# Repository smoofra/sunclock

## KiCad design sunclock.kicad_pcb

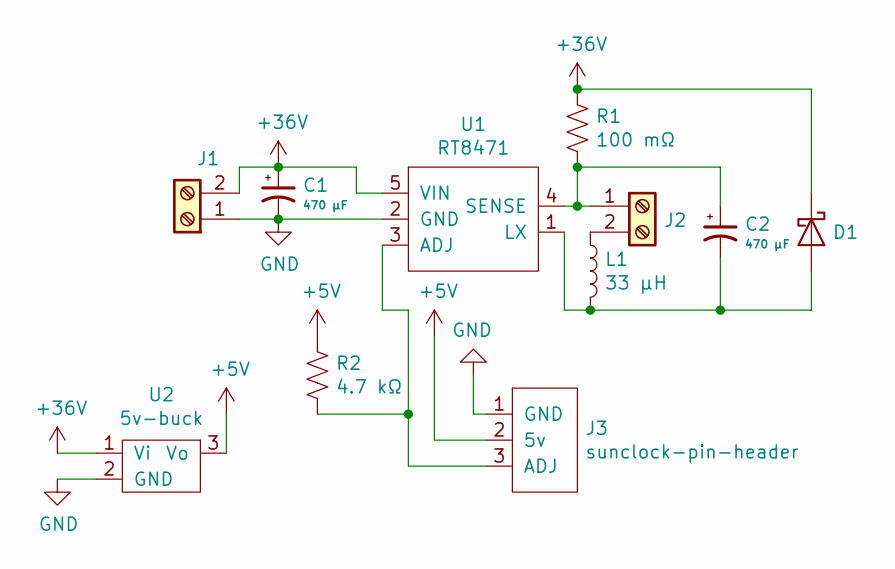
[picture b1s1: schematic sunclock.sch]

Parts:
C1, C2: 470 μF; CP_Radial_D8.0mm_P3.50mm; MPN RNE1C471MDN1PX
D1: D_Schottky; D_DO-41_SOD81_P10.16mm_Horizontal; MPN 11DQ04TR
J1, J2: Screw_Terminal_01x02; TerminalBlock_Phoenix_MKDS-1,5-2-5.08_1x02_P5.08mm_Horizont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; MPN 1935161
J3: sunclock-pin-header; SIP-3
L1: 33 μH; L_Radial_D8.7mm_P5.00mm_Fastron_07HCP; MPN RLB0914-330KL
R1: 100 mΩ; R_0402_1005Metric; MPN SR731ETTPR100F
R2: 4.7 kΩ; R_Axial_DIN0207_L6.3mm_D2.5mm_P10.16mm_Horizontal
U1: RT8471; TSOT-23-5_HandSoldering; MPN RT8471GJ5
U2: 5v-buck; SIP-3; MPN BP5277-50

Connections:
+5V: J3.2 (5v), R2.1, U2.3 (Vo)
+36V: C1.1, D1.1 (K), J1.2, R1.1, U1.5 (VIN), U2.1 (Vi)
GND: C1.2, J1.1, J3.1 (GND), U1.2 (GND), U2.2 (GND)
unnamed: C2.1, J2.1, R1.2, U1.4 (SENSE)
unnamed: C2.2, D1.2 (A), L1.2, U1.1 (LX)
unnamed: J2.2, L1.1
unnamed: J3.3 (ADJ), R2.2, U1.3 (ADJ)

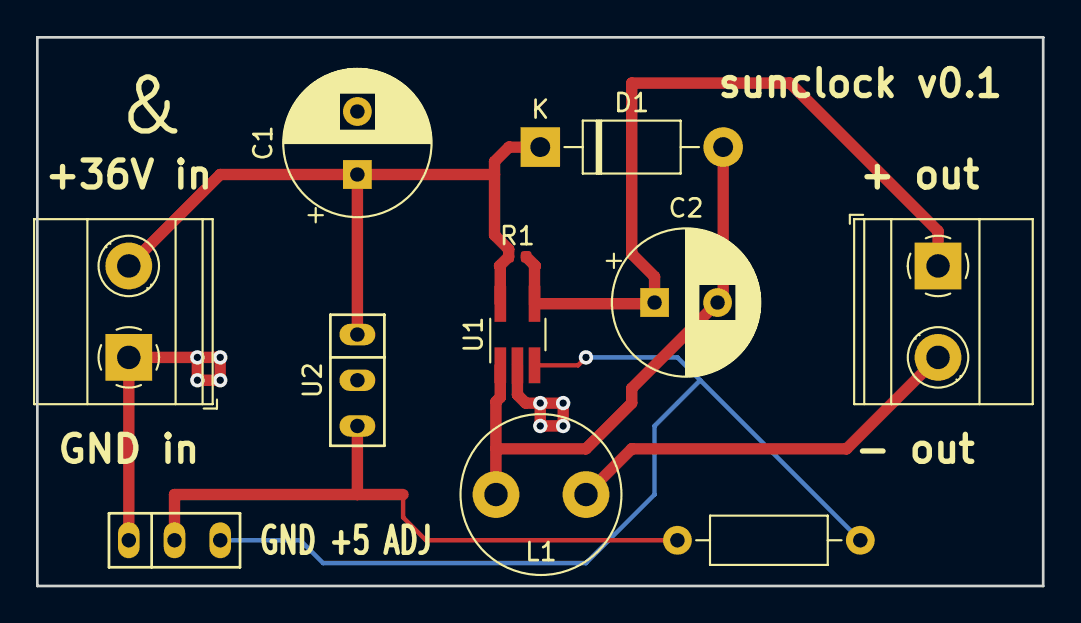
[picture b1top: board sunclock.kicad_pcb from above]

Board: 2 copper layers, 55.9 x 30.5 mm, 11 parts (0 on the bottom side), 7 nets.

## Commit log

2019-03-09 sunclock!
2019-03-09 ordered board v0.1
2019-03-09 oops, forgot to save
